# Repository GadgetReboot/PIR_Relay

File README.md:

# PIR_Relay
PIR motion sensor activated relay pcb<br><br>
<br><br>
This uses a PIR module to provide a motion activated relay that can be used to turn on a light when motion is detected in the dark.<br><br>

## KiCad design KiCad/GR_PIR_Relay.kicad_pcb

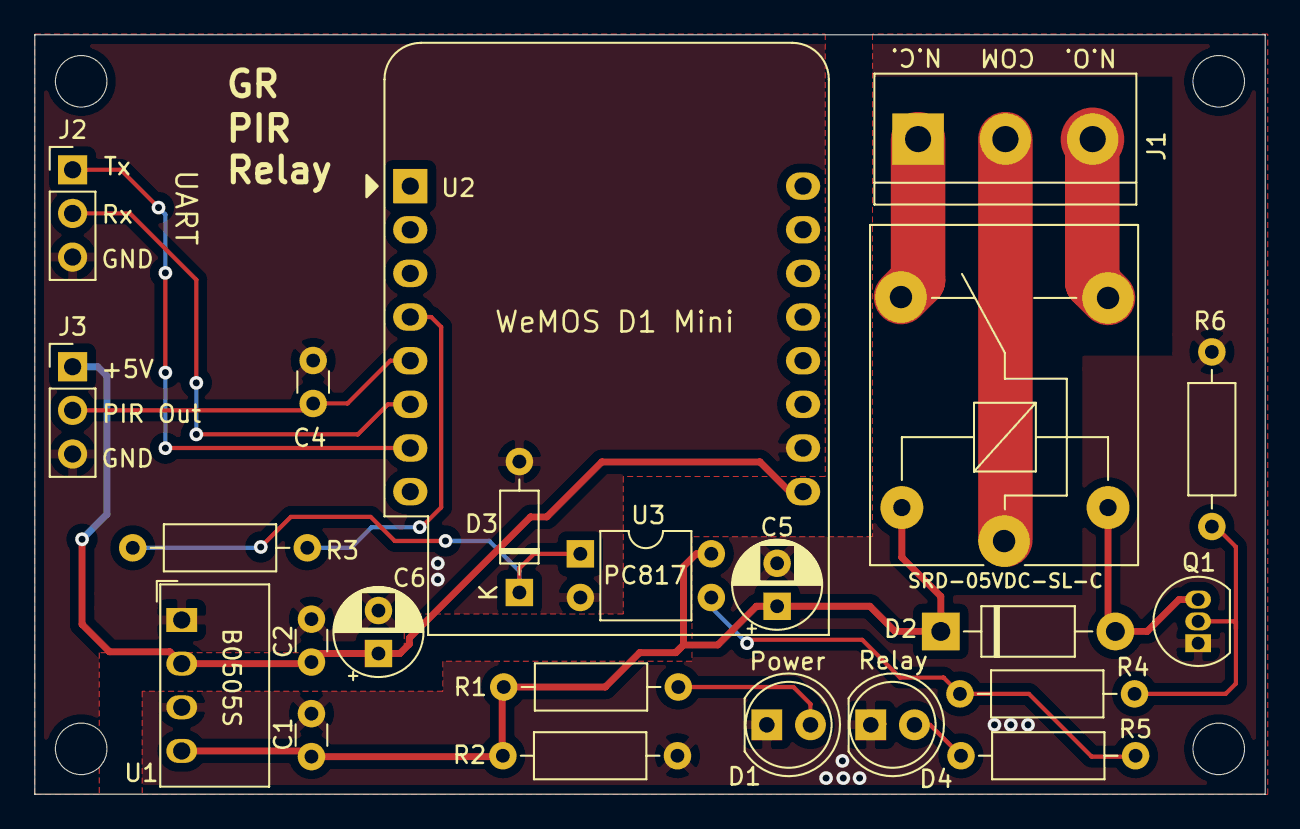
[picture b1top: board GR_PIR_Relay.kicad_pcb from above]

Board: 2 copper layers, 71.6 x 44.2 mm, 27 parts (0 on the bottom side), 17 nets.

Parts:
C1, C2: 100nF; C_Disc_D3.0mm_W1.6mm_P2.50mm
C4: 10nF; C_Disc_D3.0mm_W1.6mm_P2.50mm
C5, C6: 10uF; CP_Radial_D5.0mm_P2.50mm
D1, D4: LED_Small_ALT; LED_D5.0mm
D2: 1N4001; D_DO-41_SOD81_P10.16mm_Horizontal
D3: 1N4148; D_DO-35_SOD27_P7.62mm_Horizontal
J1: Screw_Terminal_01x03; TerminalBlock_bornier-3_P5.08mm
J2, J3: Conn_01x03; PinHeader_1x03_P2.54mm_Vertical
K1: SRD-05VDC-SL-C; Relay_SPDT_SANYOU_SRD_Series_Form_C
MH1, MH2, MH3, MH4: MountingHole; MountingHole_3mm
Q1: 2N3904; TO-92_Inline
R1, R2, R4, R5: 1K; R_Axial_DIN0207_L6.3mm_D2.5mm_P10.16mm_Horizontal
R3: 470r; R_Axial_DIN0207_L6.3mm_D2.5mm_P10.16mm_Horizontal
R6: 100K; R_Axial_DIN0207_L6.3mm_D2.5mm_P10.16mm_Horizontal
U1: B0505S; Converter_DCDC_muRata_CRE1xxxxxx3C_THT
U2: WeMos_D1_mini; WEMOS_D1_mini_light
U3: PC817; DIP-4_W7.62mm

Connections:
+5V: C1.1, C5.1, D2.1, K1.5, R1.2, R2.2, U1.4, U3.4
+5VD: C2.1, C6.1, J3.1, U1.2, U2.9
/PIR: C4.1, J3.2, U2.5
/Relay: R4.2, R5.2, U3.3
/Relay_Ctrl: R3.2, U2.4
/RxD: J2.2, U2.6
/TxD: J2.1, U2.7
GND: C1.2, C5.2, D1.1, D4.1, Q1.1, R2.1, R6.1, U1.3
GNDREF: C2.2, C4.2, C6.2, D3.2, J2.3, J3.3, U1.1, U2.10, U3.2
unnamed: D1.2, R1.1
unnamed: D2.2, K1.2, Q1.3
unnamed: D3.1, R3.1, U3.1
unnamed: D4.2, R5.1
unnamed: J1.1, K1.4
unnamed: J1.2, K1.1
unnamed: J1.3, K1.3
unnamed: Q1.2, R4.1, R6.2
